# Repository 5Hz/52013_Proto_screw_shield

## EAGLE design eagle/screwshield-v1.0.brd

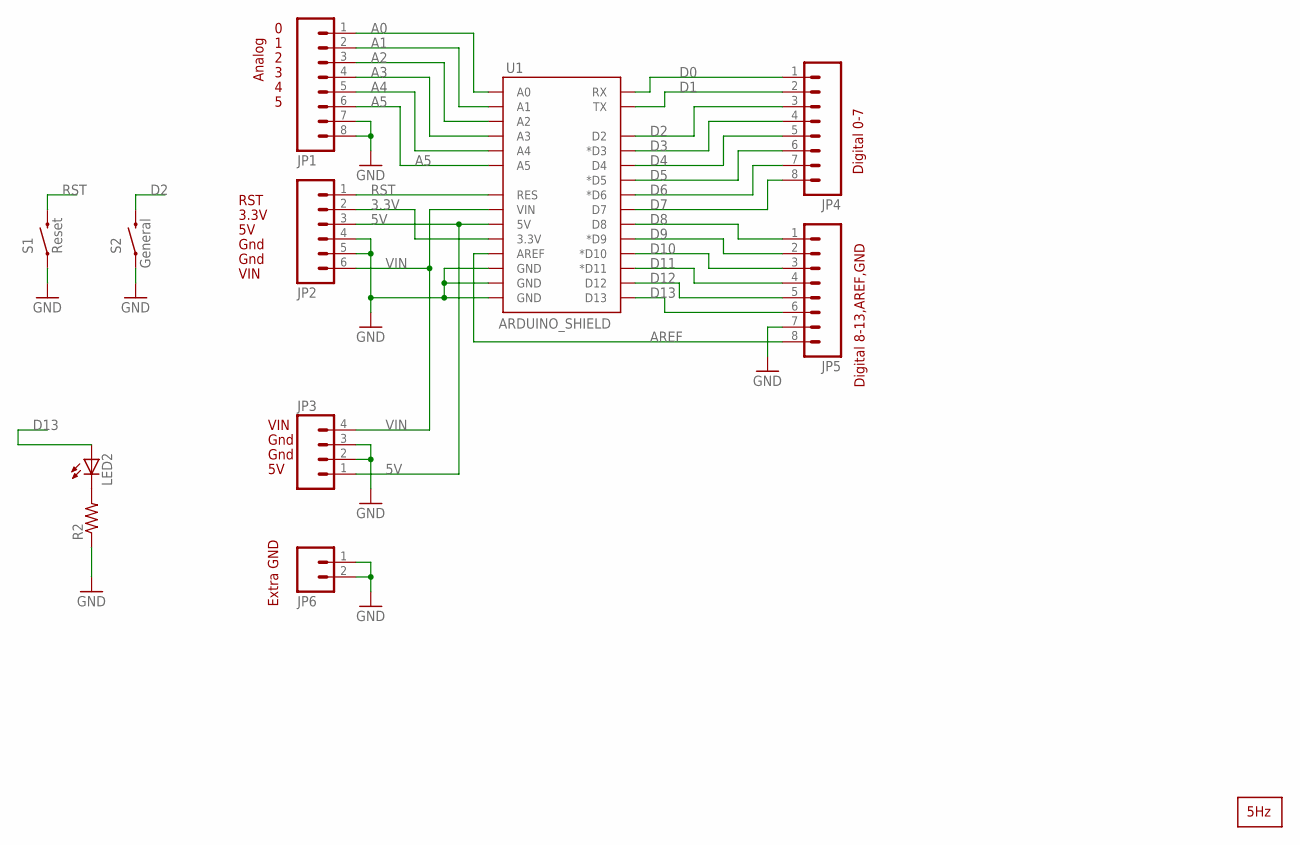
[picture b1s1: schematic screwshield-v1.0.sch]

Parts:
JP1, JP4, JP5: M083.5MM-8; SCREWTERMINAL-3.5MM-8
JP2: M063.5MM-6; SCREWTERMINAL-3.5MM-6
JP3: M04SCREW; SCREWTERMINAL-3.5MM-4
JP6: M023.5MM; SCREWTERMINAL-3.5MM-2
LED2: LED0603; LED-0603
R2: RESISTOR0603-RES; 0603-RES
S1: Reset; TACTILE-PTH
S2: General; TACTILE-PTH
U1: ARDUINO_SHIELD; DUEMILANOVE_SHIELD_NOHOLES
U$1: LOGO_SILKL15MM; LARGO_15MM

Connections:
3.3V: JP2.2, U1.3.3V
5V: JP2.3, JP3.1, U1.5V
A0: JP1.1, U1.A0
A1: JP1.2, U1.A1
A2: JP1.3, U1.A2
A3: JP1.4, U1.A3
A4: JP1.5, U1.A4
A5: JP1.6, U1.A5
AREF: JP5.8, U1.AREF
D0: JP4.1, U1.RX
D1: JP4.2, U1.TX
D2: JP4.3, S2.3 (2), U1.D2
D3: JP4.4, U1.D3 (*D3)
D4: JP4.5, U1.D4
D5: JP4.6, U1.D5 (*D5)
D6: JP4.7, U1.D6 (*D6)
D7: JP4.8, U1.D7
D8: JP5.1, U1.D8
D9: JP5.2, U1.D9 (*D9)
D10: JP5.3, U1.D10 (*D10)
D11: JP5.4, U1.D11 (*D11)
D12: JP5.5, U1.D12
D13: JP5.6, LED2.A, U1.D13
GND: JP1.7, JP1.8, JP2.4, JP2.5, JP3.2, JP3.3, JP5.7, JP6.1, JP6.2, R2.1, S1.1, S2.1, U1.GND@0 (GND), U1.GND@1 (GND), U1.GND@2 (GND)
unnamed: LED2.C, R2.2
RST: JP2.1, S1.3 (2), U1.RES
VIN: JP2.6, JP3.4, U1.VIN

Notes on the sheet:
Analog
Gnd
VIN
3.3V
RST
Digital 8-13,AREF,GND
Digital 0-7
Extra GND

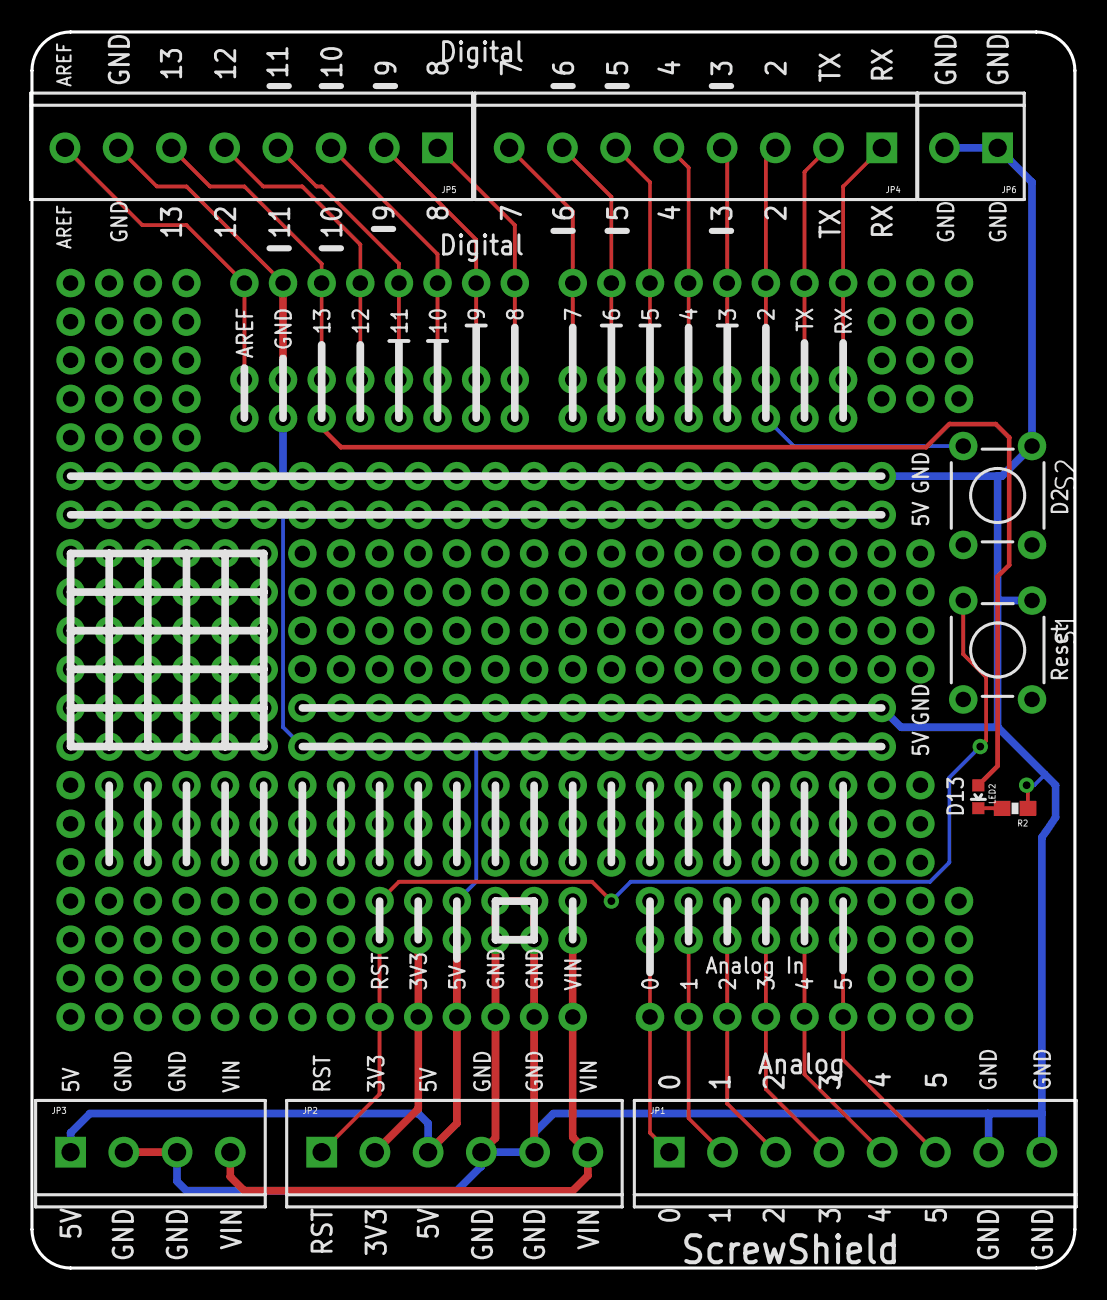
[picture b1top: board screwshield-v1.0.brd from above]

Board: 2 copper layers, 68.6 x 81.3 mm, 12 parts (1 on the bottom side), 27 nets.

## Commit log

2014-01-14 creación
